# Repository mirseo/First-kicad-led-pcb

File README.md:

### Creating an LED PCB

[한국어](README-ko.md)

This project involves designing a PCB using KiCad.  
I decided to learn about PCB design to achieve a specific goal, and it turned out to be a great opportunity.  
This is just the beginning, so I plan to keep studying hard.  

### Layout (PCB Design)

PIN_Header : Connector_PinHeader_1.00mm:PinHeader_2x01_P1.00mm_Vertical  
LED : LED_THT:LED_D5.0mm  
Resistor : Resistor_THT:R_Axial_DIN0204_L3.6mm_D1.6mm_P5.08mm_Horizontal

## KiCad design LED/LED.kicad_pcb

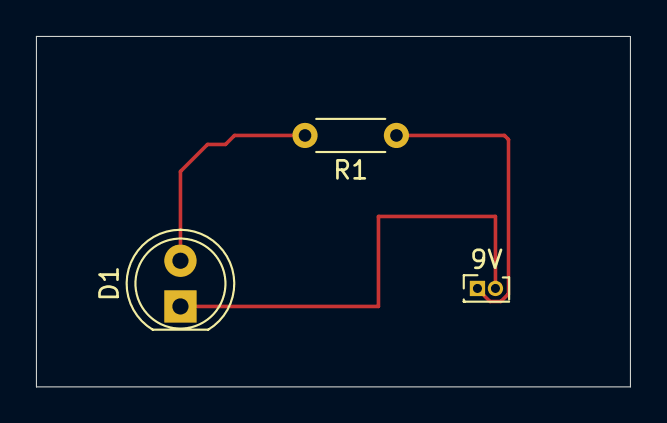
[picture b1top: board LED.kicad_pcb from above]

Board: 2 copper layers, 33.0 x 19.5 mm, 3 parts (0 on the bottom side), 3 nets.

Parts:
9V: Battery; PinHeader_2x01_P1.00mm_Vertical
D1: LED; LED_D5.0mm
R1: 470; R_Axial_DIN0204_L3.6mm_D1.6mm_P5.08mm_Horizontal

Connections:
unnamed: 9V.1 (+), R1.1
unnamed: 9V.2 (-), D1.1 (K)
unnamed: D1.2 (A), R1.2
